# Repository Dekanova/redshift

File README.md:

# Redshift 

This is the central repository for work on the Redshift PCB.

## Features
- 8kHz polling (USB 2.0 HighSpeed)
- usb-C port
- PAW 3399

## Usage
- KiCad 6.0+ must be installed
- Openinput library from kicad content&lib manager in KiCad

**NOTE:** Encoder 3d file is intentionally not included. If you wish to add it, models are freely downloaded from Alps Alpine [website](https://tech.alpsalpine.com/e/products/cad.html) under EC10E.

## Board Notes
- If connecting USB and debug connectors at the same time, ensure debug supply voltage is under 5v. (some JTAG debuggers have this) 5v supply from debug pins are OK as long as USB is unplugged.
- PcbNew grid size used is 0.1mm

### Credits
A huge thanks to openinput for their generic [KiCad lib](https://github.com/openinput-fw/openinput-kicad-library), as well as their [fully developed PCBs](https://github.com/openinput-fw/sammy) which this PCB is largely based off of.

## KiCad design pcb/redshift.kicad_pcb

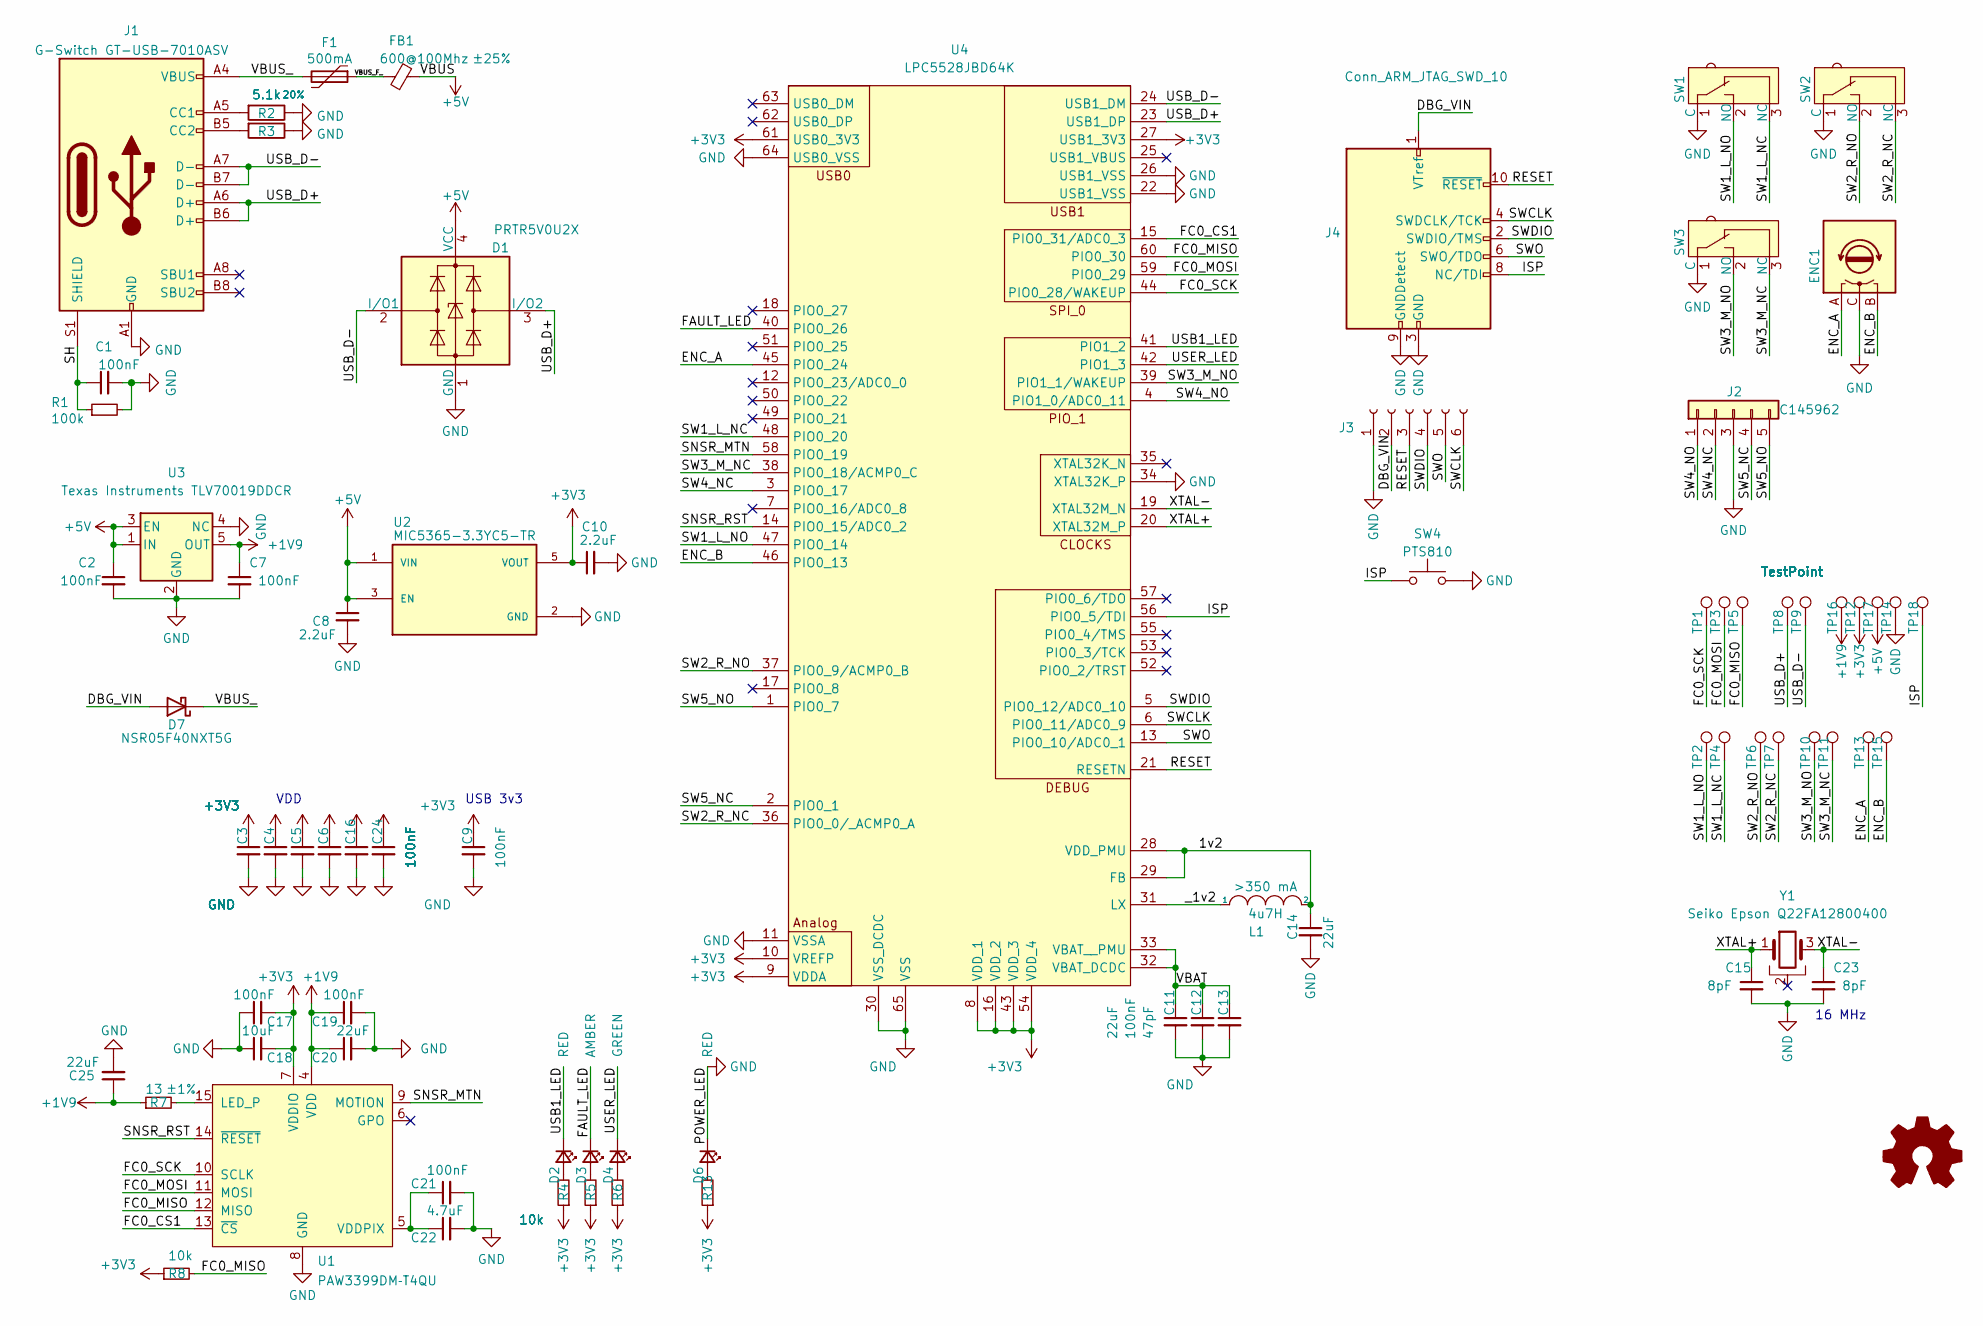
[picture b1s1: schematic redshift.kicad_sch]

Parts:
C1, C2, C3, C4, C5, C6, C7, C9, C12, C16, C17, C19, C21, C24: 100nF; C_0402_1005Metric; LCSC C1525
C8, C10: 2.2uF; C_0402_1005Metric; LCSC C12530
C11, C14, C20, C25: 22uF; C_0603_1608Metric; LCSC C59461
C13: 47pF; C_0402_1005Metric; LCSC C1567
C15, C23: 8pF; C_0402_1005Metric; LCSC C1578
C18: 10uF; C_0402_1005Metric; LCSC C15525
C22: 4.7uF; C_0402_1005Metric; LCSC C23733
D1: PRTR5V0U2X; BF994S; LCSC C12333
D2, D6: RED; LED_0402_1005Metric; LCSC C965790
D3: AMBER; LED_0402_1005Metric; LCSC C401111
D4: GREEN; LED_0402_1005Metric; LCSC C401111
D7: NSR05F40NXT5G; D_0402_1005Metric; LCSC C146713
ENC1: Rotary_Encoder; RotaryEncoder_Horizontal
F1: 500mA; Fuse_0402_1005Metric; LCSC C17168
FB1: 600@100Mhz; L_0402_1005Metric; Tolerance ±25%; LCSC C142082
J1: G-Switch GT-USB-7010ASV; GCT_USB4105-GF-A; LCSC C2988369
J2: C145962; JST_SH_BM05B-SRSS-TB_1x05-1MP_P1.00mm_Vertical
J3: C2935905; PinHeader_1x06_P2.00mm_Vertical
J4: Conn_ARM_JTAG_SWD_10; PinHeader_2x05_P1.27mm_Vertical_SMD; LCSC C2935458
L1: 4u7H; L_0805_2012Metric; LCSC C63166
R1: 100k; R_0402_1005Metric; LCSC C25741
R2, R3: 5.1k; R_0402_1005Metric; Tolerance 20%; LCSC C25905
R4, R5, R6, R8, R13: 10k; R_0402_1005Metric; LCSC C25744
R7: 13; R_0402_1005Metric; Tolerance ±1%; LCSC C368403
SW1, SW2, SW3: SW_SP; SW_Micro_Switch
SW4: PTS810; SW_SPST_B3U-1000P; LCSC C231329
TP1, TP2, TP3, TP4, TP5, TP6, TP7, TP8, TP9, TP10, TP11, TP12, TP13, TP14, TP15, TP16, TP17, TP18: TestPoint; TestPoint_Pad_D1.5mm
U1: PAW3399DM‐T4QU; PXI-DIP-16
U2: MIC5365-3.3YC5-TR; SOT-23-5; PARTREV 3.1 - July 16, 2013; LCSC C82942
U3: Texas Instruments TLV70019DDCR; SOT-23-5; LCSC C507266
U4: LPC5528JBD64K; QFP50P1200X1200X120-65N
Y1: Seiko Epson Q22FA12800400; LCSC C255875

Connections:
+1V9: C7.1, C19.1, C20.1, C25.1, R7.1, TP16.1, U1.4 (VDD), U3.5 (OUT)
+3V3: C3.1, C4.1, C5.1, C6.1, C9.1, C10.1, C16.1, C17.2, C18.2, C24.1, R4.1, R5.1, R6.1, R8.1, R13.1, TP12.1, U1.7 (VDDIO), U2.5 (VOUT), U4.8 (VDD_1), U4.9 (VDDA), U4.10 (VREFP), U4.16 (VDD_2), U4.27 (USB1_3V3), U4.43 (VDD_3), U4.54 (VDD_4), U4.61 (USB0_3V3)
+5V: C2.1, C8.1, D1.4 (VCC), FB1.2, TP17.1, U2.1 (VIN), U2.3 (EN), U3.1 (IN), U3.3 (EN)
/1v2: C14.1, L1.2, U4.28 (VDD_PMU), U4.29 (FB)
/DBG_VIN: D7.2 (A), J3.2, J4.1 (VTref)
/ENC_A: ENC1.A, TP13.1, U4.45 (PIO0_24)
/ENC_B: ENC1.B, TP15.1, U4.46 (PIO0_13)
/FAULT_LED: D3.1 (K), U4.40 (PIO0_26)
/FC0_CS1: U1.13 (~CS), U4.15 (PIO0_31/ADC0_3)
/FC0_MISO: R8.2, TP5.1, U1.12 (MISO), U4.60 (PIO0_30)
/FC0_MOSI: TP3.1, U1.11 (MOSI), U4.59 (PIO0_29)
/FC0_SCK: TP1.1, U1.10 (SCLK), U4.44 (PIO0_28/WAKEUP)
/ISP: J4.8 (NC/TDI), SW4.1, TP18.1, U4.56 (PIO0_5/TDI)
/RESET: J3.3, J4.10 (~RESET), U4.21 (RESETN)
/SH: C1.1, J1.S1 (SHIELD), J1.S2 (SHIELD), J1.S3 (SHIELD), J1.S4 (SHIELD), R1.1
/SNSR_MTN: U1.9 (MOTION), U4.58 (PIO0_19)
/SNSR_RST: U1.14 (~RESET), U4.14 (PIO0_15/ADC0_2)
/SW1_L_NC: SW1.3 (NC), TP4.1, U4.48 (PIO0_20)
/SW1_L_NO: SW1.2 (NO), TP2.1, U4.47 (PIO0_14)
/SW2_R_NC: SW2.3 (NC), TP7.1, U4.36 (PIO0_0/_ACMP0_A)
/SW2_R_NO: SW2.2 (NO), TP6.1, U4.37 (PIO0_9/ACMP0_B)
/SW3_M_NC: SW3.3 (NC), TP11.1, U4.38 (PIO0_18/ACMP0_C)
/SW3_M_NO: SW3.2 (NO), TP10.1, U4.39 (PIO1_1/WAKEUP)
/SW4_NC: J2.2, U4.3 (PIO0_17)
/SW4_NO: J2.1, U4.4 (PIO1_0/ADC0_11)
/SW5_NC: J2.4, U4.2 (PIO0_1)
/SW5_NO: J2.5, U4.1 (PIO0_7)
/SWCLK: J3.6, J4.4 (SWDCLK/TCK), U4.6 (PIO0_11/ADC0_9)
/SWDIO: J3.4, J4.2 (SWDIO/TMS), U4.5 (PIO0_12/ADC0_10)
/SWO: J3.5, J4.6 (SWO/TDO), U4.13 (PIO0_10/ADC0_1)
/USB1_LED: D2.1 (K), U4.41 (PIO1_2)
/USB_D+: D1.3 (I/O2), J1.A6 (D+), J1.B6 (D+), TP8.1, U4.23 (USB1_DP)
/USB_D-: D1.2 (I/O1), J1.A7 (D-), J1.B7 (D-), TP9.1, U4.24 (USB1_DM)
/USER_LED: D4.1 (K), U4.42 (PIO1_3)
/VBAT: C11.1, C12.1, C13.1, U4.32 (VBAT_DCDC), U4.33 (VBAT__PMU)
/VBUS_: D7.1 (K), F1.2, J1.A4 (VBUS), J1.A9 (VBUS), J1.B4 (VBUS), J1.B9 (VBUS)
/VBUS_F_: F1.1, FB1.1
/XTAL+: C15.1, U4.20 (XTAL32M_P), Y1.1
/XTAL-: C23.1, U4.19 (XTAL32M_N), Y1.3
/_1v2: L1.1, U4.31 (LX)
GND: C1.2, C2.2, C3.2, C4.2, C5.2, C6.2, C7.2, C8.2, C9.2, C10.2, C11.2, C12.2, C13.2, C14.2, C15.2, C16.2, C17.1, C18.1, C19.2, C20.2, C21.2, C22.2, C23.2, C24.2, C25.2, D1.1 (GND), D6.1 (K), ENC1.C, J1.A1 (GND), J1.A12 (GND), J1.B1 (GND), J1.B12 (GND), J2.3, J3.1, J4.3 (GND), J4.5 (GND), J4.9 (GNDDetect), R1.2, R2.1, R3.1, SW1.1 (C), SW2.1 (C), SW3.1 (C), SW4.2, TP14.1, U1.3 (GND), U1.8 (GND), U2.2 (GND), U3.2 (GND), U3.4 (NC), U4.11 (VSSA), U4.22 (USB1_VSS), U4.26 (USB1_VSS), U4.30 (VSS_DCDC), U4.34 (XTAL32K_P), U4.64 (USB0_VSS), U4.65 (VSS)
unnamed: C21.1, C22.1, U1.5 (VDDPIX)
unnamed: D2.2 (A), R4.2
unnamed: D3.2 (A), R5.2
unnamed: D4.2 (A), R6.2
unnamed: D6.2 (A), R13.2
unnamed: J1.A5 (CC1), R2.2
unnamed: J1.B5 (CC2), R3.2
unnamed: R7.2, U1.15 (LED_P)

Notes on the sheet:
USB 3v3
VDD
16 MHz

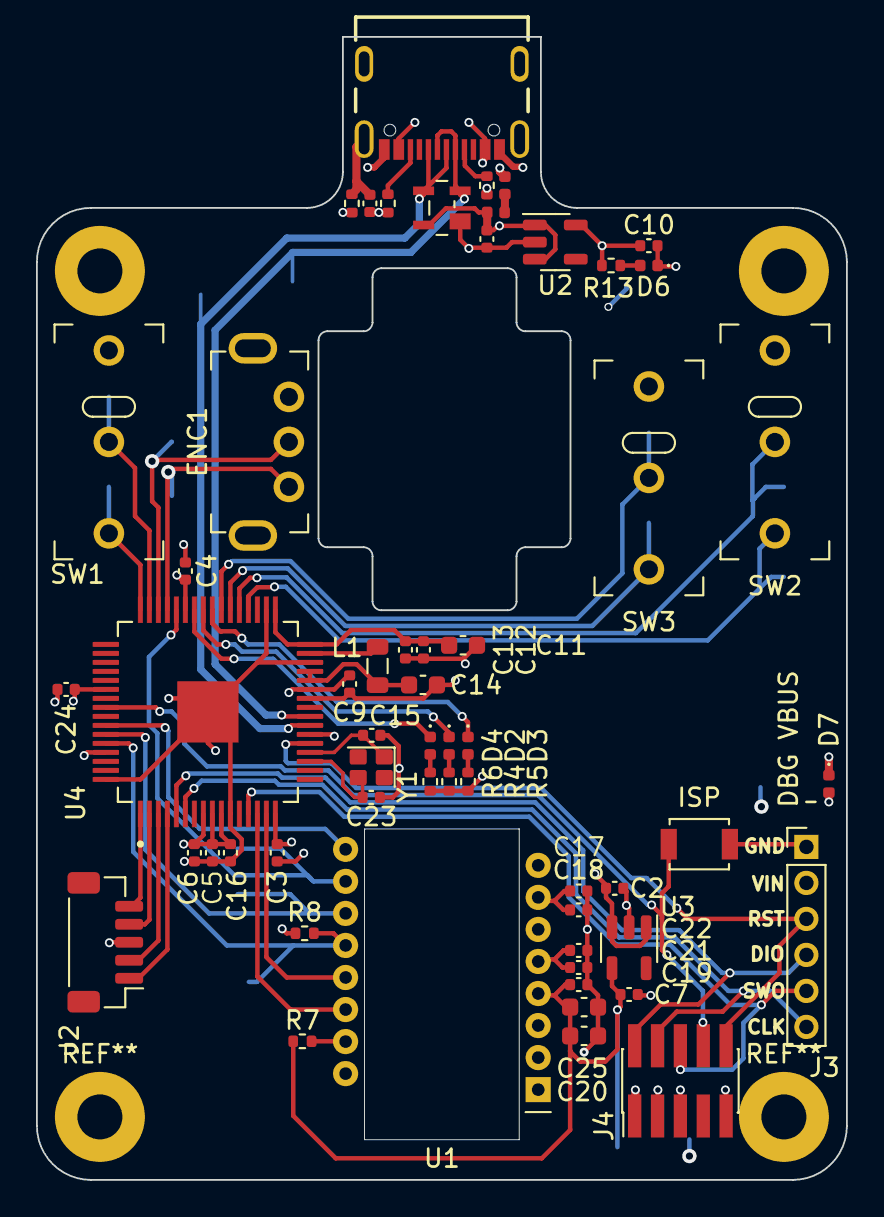
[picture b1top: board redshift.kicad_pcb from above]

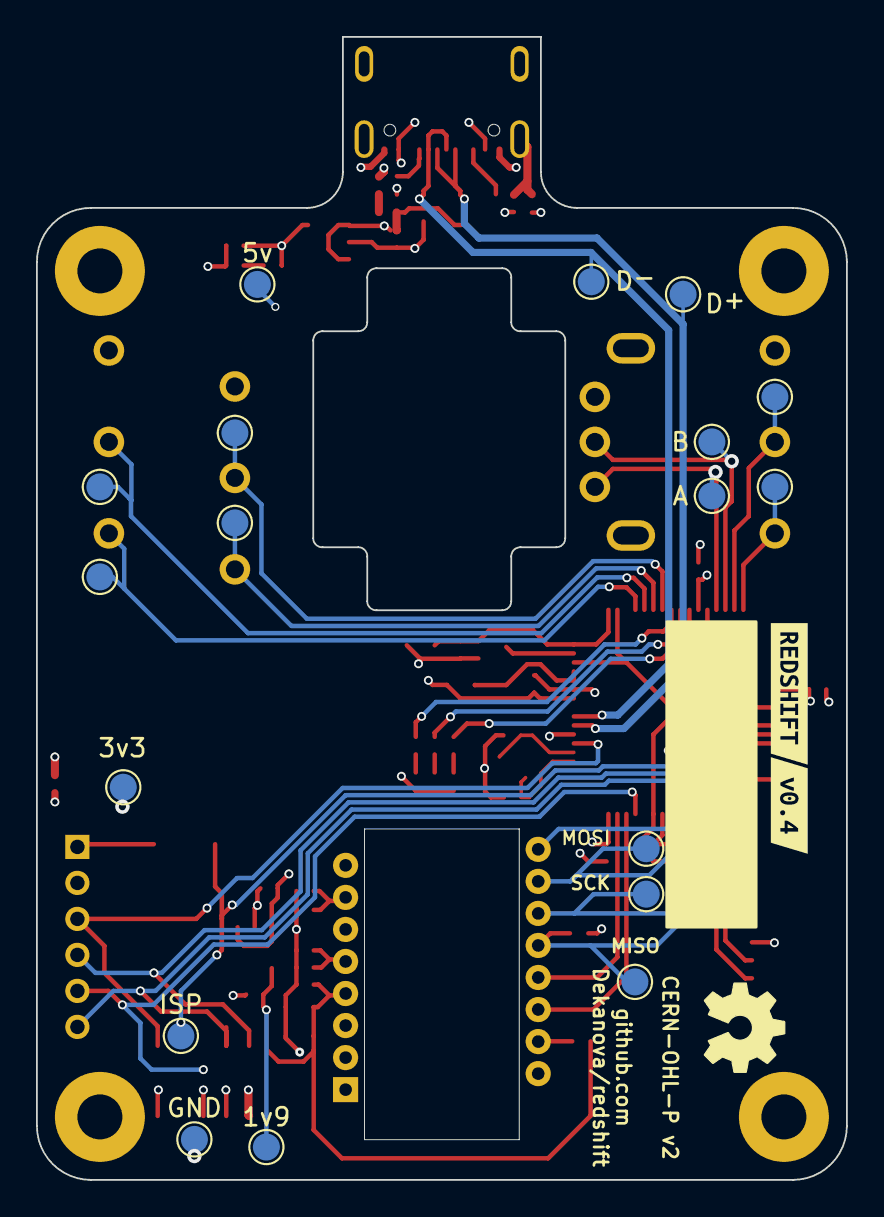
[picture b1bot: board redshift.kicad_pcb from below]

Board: 4 copper layers, 45.0 x 63.5 mm, 77 parts (20 on the bottom side), 49 nets.

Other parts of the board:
kibuzzard-63C8EA46: G***; kibuzzard-63C8EA46
kibuzzard-637894B3: G***; kibuzzard-637894B3

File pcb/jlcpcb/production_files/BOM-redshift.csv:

Comment,Designator,Footprint,LCSC
4u7H,L1,R_0603_1608Metric,C1034
PRTR5V0U2X,D1,BF994S,C12333
2.2uF,"C10,C8",C_0402_1005Metric,C12530
C145962,J2,JST_SH_BM05B-SRSS-TB_1x05-1MP_P1.00mm_Vertical,C145962
NSR05F40NXT5G,D7,D_0402_1005Metric,C146713
100nF,"C1,C12,C16,C17,C19,C2,C21,C24,C3,C4,C5,C6,C7,C9",C_0402_1005Metric,C1525
10uF,C18,C_0402_1005Metric,C15525
47pF,C13,C_0402_1005Metric,C1567
8pF,"C15,C23",C_0402_1005Metric,C1578
PTS810,SW4,SW_SPST_B3U-1000P,C231329
4.7uF,C22,C_0402_1005Metric,C23733
Seiko Epson Q22FA12800400,Y1,Seiko Epson Q22FA12800400,C255875
100k,R1,R_0402_1005Metric,C25741
10k,"R13,R4,R5,R6,R8",R_0402_1005Metric,C25744
5.1k,"R2,R3",R_0402_1005Metric,C25905
Conn_ARM_JTAG_SWD_10,J4,PinHeader_2x05_P1.27mm_Vertical_SMD,C2935458
C2935905,J3,PinHeader_1x06_P2.00mm_Vertical,C2935905
G-Switch GT-USB-7010ASV,J1,GCT_USB4105-GF-A,C2988369
13+-1%,R7,R_0402_1005Metric,C368403
AMBER,"D3,D4",LED_0402_1005Metric,C401111
Texas Instruments TLV70028DDCR,U3,SOT-23-5,C507266
~,FB1,L_0402_1005Metric,C524454
22uF,"C11,C14,C20,C25",C_0603_1608Metric,C59461
500mA,F1,Fuse_0402_1005Metric,C710338
MIC5365-3.3YC5-TR,U2,SOT-23-5,C82942
RED,"D2,D6",LED_0402_1005Metric,C965790
LPC5526JEV98,IC1,BGA98C50P13X13_700X700X97N,

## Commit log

2021-11-30 add licence
2021-11-30 fix git files
2021-12-02 add USB and some power wires
2021-12-05 route USB and power lines, fix ESD chip
2021-12-11 add trace header and LEDs
2021-12-11 add pictures to README
2021-12-23 pre v0.1
2022-01-17 add lpc55 footprint from solokeys, release v0.1
2022-01-17 Add GCT usb-C 2.0 port footprint to local project
2022-01-22 Update README.md
    Spelling.
2022-02-16 add ISP pin
2022-03-06 fix #2, add missing lib source
2022-03-06 update encoder footprint fixes #5
2022-03-06 update USB footprint, remove pad inside SWDIO trace
2022-03-10 Debug fixes
    - add 10 pin debug connector
    - remove uneeded pull up resistors on pins (MCU has internal ones)
    - add a diode to protect reverse current on the debug pins
2022-03-12 widen USB pair to within spec
2022-03-21 bump version, use proper spec Caps
2022-03-21 bump version for archive
2022-09-18 ground unused USB line per datasheet, use smaller switch for ISP
2022-09-18 Replaced Old LDO
2022-09-19 Added cheap and slightly larger 3.3v LDO
2022-09-19 Returned overwritten library path back to normal
2022-09-26 Added the only missing lib I could find: the mcu
2022-09-26 Remove old ldo lib
2022-10-02 First
2022-10-02 Fixed VDD/IO, LED_P, and removed Sensor LED from Schematic
2022-10-02 Modified PCB to reflect changes Moved some silkscreens and parts around to fit better Changed default VIA size to match what's being used
2022-10-07 Test Kibot CI
2022-10-08 Remove #auto_saved_files# and add it to .gitignore
2022-10-08 Change +1V8 To +1V9 Also align everything to a 50 mil grid
2022-10-08 Saved
2022-10-24 Add missing 3D Models Replace missing 3D models with similar ones Add some models to gitignore
2022-11-10 Change design constraints to better match JLC Fix all DRC errors
2022-11-11 Small Changes to USB Footprint Make USB test points hopefully less detrimental
2022-11-12 Update USB data lines to be ~90 ohms
2022-11-13 Give all components LCSC listings Change some components to match stock
2022-11-13 Add ground fill to top and bottom
2022-11-13 Assign the JTAG connecter to a LCSC part
2022-11-13 Add random VIAs to help ground planes connect
2022-11-13 Forgot to save, look at previous
2022-11-13 Change 3.3v LDO LCSC part, original had 3 pins
2022-11-14 Test generating JLC files again
2022-11-14 remove top and bottom fill, small naming fixes
2022-11-15 Fixes #25
2022-11-16 Swap Ferrite Bead
2022-11-16 Place JTAG/SWO Connector Put 0Ω Resistor in Fuse Place Find LCSC Part for 13Ω Resistor
2022-11-16 Remove C145962 from Parts List
2022-11-17 Fix small silkscreen error Remove uneccesary AR-Check file
2022-11-19 small fixes and updating board from schmatic
2022-11-19 update ibom
2022-11-19 remove jlcpcb output from git
2022-11-20 Add part numbers back based off of 64fe10091f3e64ca899d2226f0a24cf256eb9be7
2023-01-07 Added Symbol for new chip to schematic
2023-01-07 Reconnected paths that prev lead to deleted pins
2023-01-07 Progress on the PCB routing
2023-01-07 Routing basically done
2023-01-08 Finished routing Finished Silkscreen placement
2023-01-08 Change README
2023-01-09 refactor mcu layout for better clarity
2023-01-09 Add grid size note to readme
2023-01-19 small fixes, add mounting holes
2023-08-04 fix sensor LDO pins & pull down MCU power caps instead of up

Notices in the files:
pcb/redshift.kicad_pcb:
This source describes Open Hardware and is licensed under the CERN-OHL-Rv2
Copyright (c) Dekanova LLC
CERN-OHL-P v2
parts and their libraries:
Copyright 2021 Accelerated Designs. All rights reserved.
